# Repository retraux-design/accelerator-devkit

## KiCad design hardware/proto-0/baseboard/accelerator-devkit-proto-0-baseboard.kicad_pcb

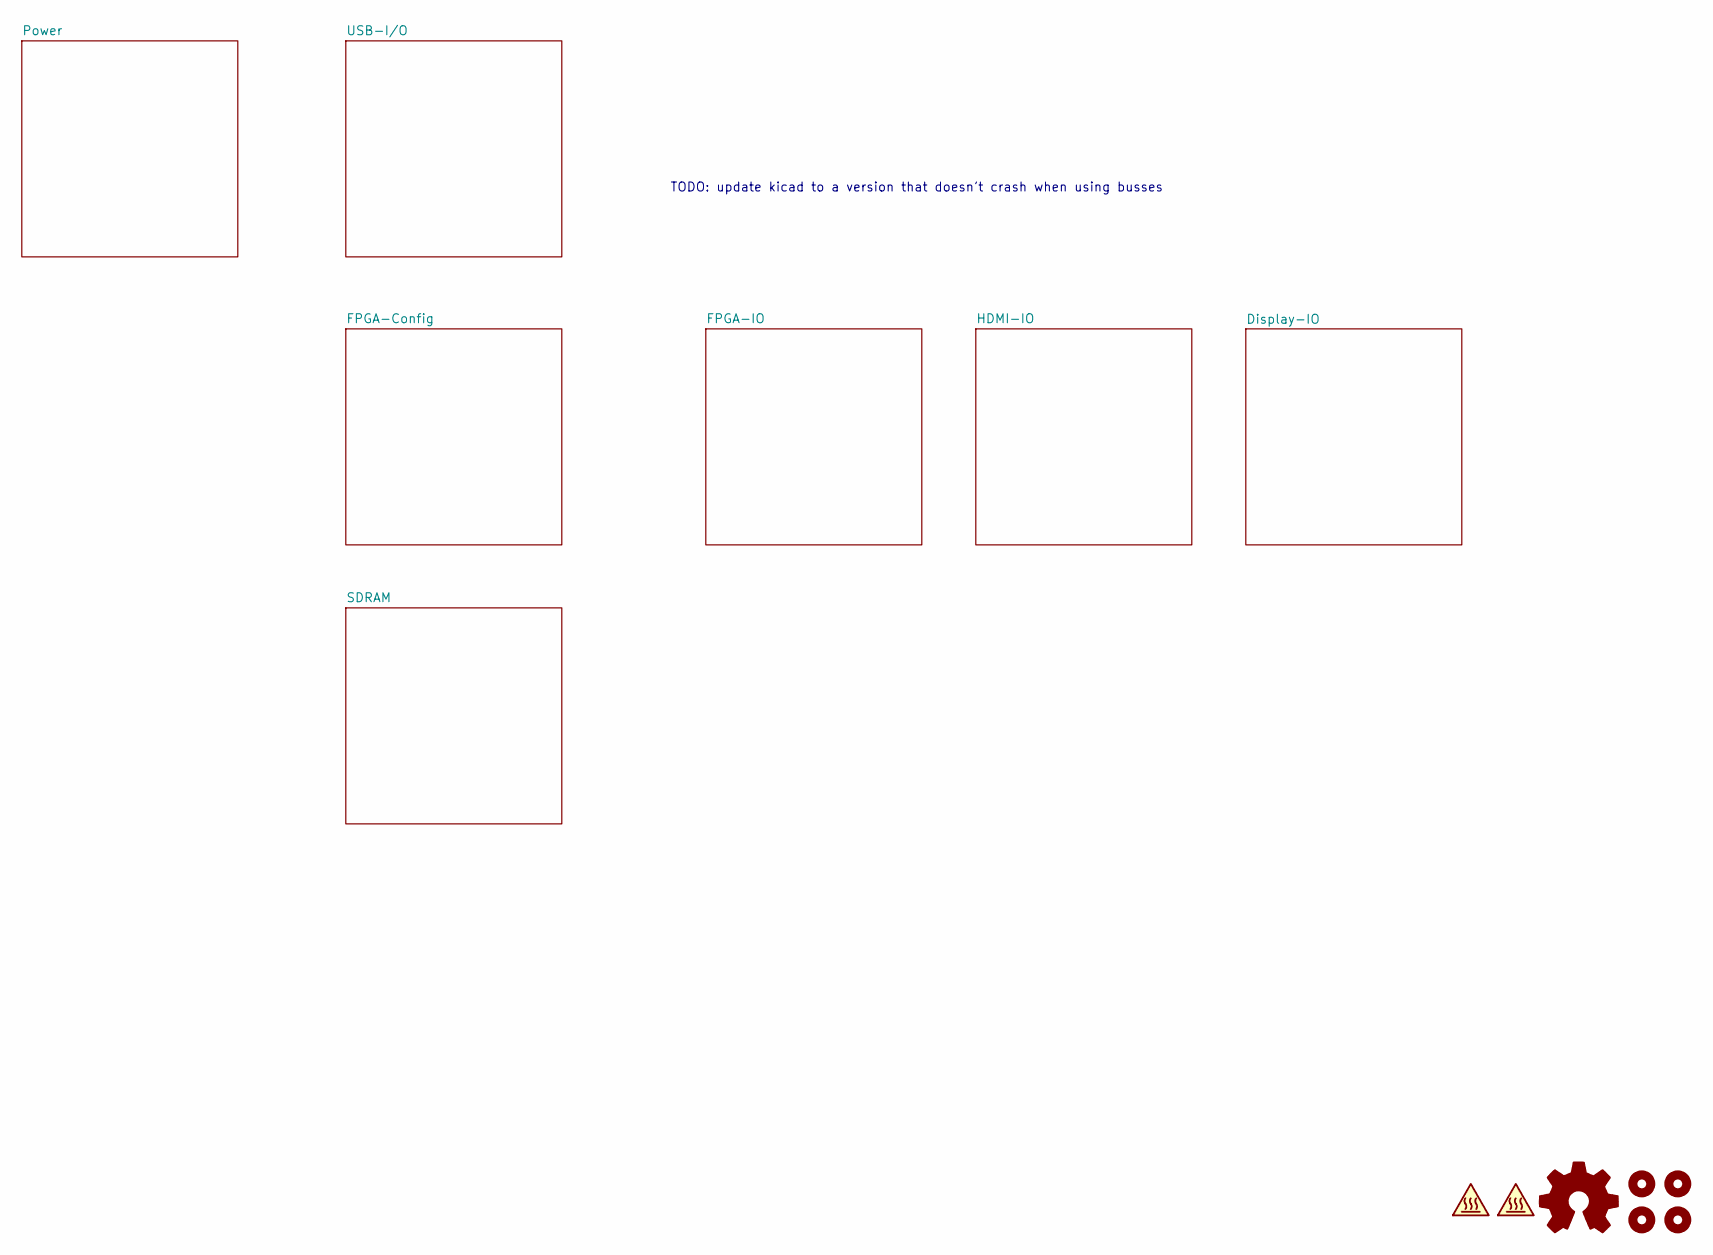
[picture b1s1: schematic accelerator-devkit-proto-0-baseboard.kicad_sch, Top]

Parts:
H1, H2, H3, H4: MountingHole; MountingHole_2.2mm_M2_Pad_Via
LOGO1: Logo_Open_Hardware_Small; OSHW-Symbol_6.7x6mm_Copper
LOGO2, LOGO3: SYM_Hot_Small; OSHW-Logo2_7.3x6mm_Copper

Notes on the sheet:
TODO: update kicad to a version that doesn't crash when using busses

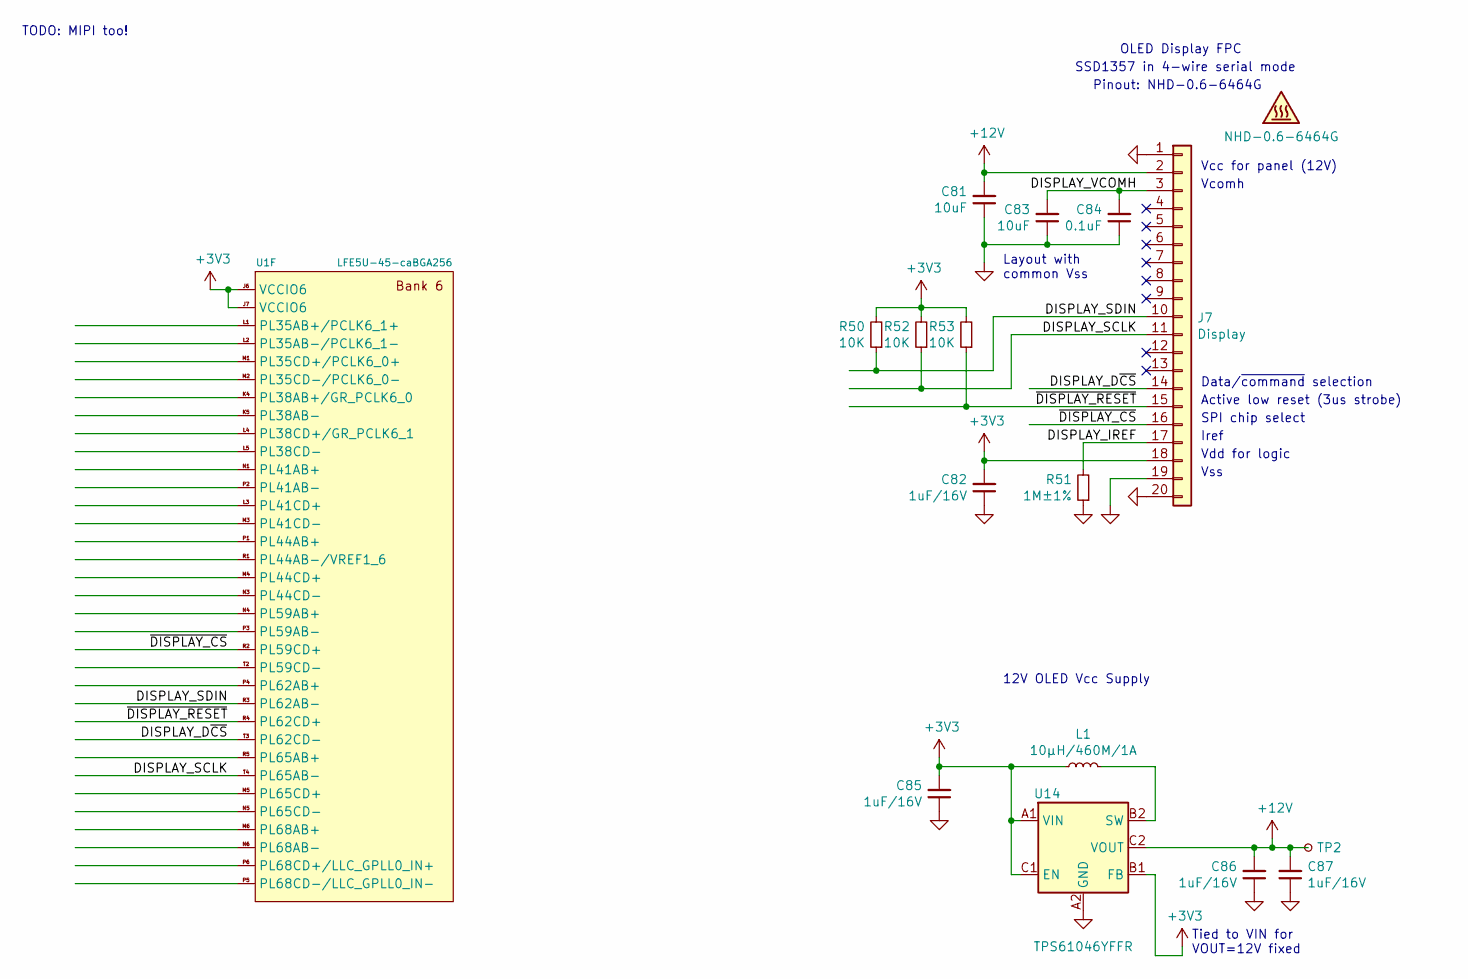
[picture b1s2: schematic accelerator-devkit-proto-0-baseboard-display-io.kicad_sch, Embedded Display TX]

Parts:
C81, C83: 10uF; C_0402_1005Metric
C82, C85, C86, C87: 1uF/16V; C_0402_1005Metric
C84: 0.1uF; C_0402_1005Metric
DISPLAY1: NHD-0.6-6464G
J7: Display; Molex_FFC-FPC_52745-2033_1x20_P0.5mm_TopContact
L1: 10µH/460M/1A; L_1008_2520Metric; Part 1239AS-H-100M=P2
R50, R52, R53: 10K; R_0402_1005Metric
R51: 1M±1%; R_0402_1005Metric
TP2: TestPoint_Small; TestPoint_THTPad_D1.0mm_Drill0.5mm
U1: LFE5U-45-caBGA256; Lattice_caBGA-256_14x14mm_P0.8mm
U14: TPS61046YFFR; Texas_DSBGA-6_0.8x1.2mm_Layout2x3_P0.4mm

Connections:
+3V3: C82.2, C85.2, J7.18, L1.1, R50.2, R52.2, R53.2, U1.J6 (VCCIO6), U1.J7 (VCCIO6), U14.A1 (VIN), U14.B1 (FB), U14.C1 (EN); also elsewhere on the board
+12V: C81.2, C86.2, C87.2, J7.2, TP2.1, U14.C2 (VOUT)
/Display-IO/DISPLAY_D~CS: J7.14, U1.T3 (PL62CD-)
/Display-IO/DISPLAY_IREF: J7.17, R51.2
/Display-IO/DISPLAY_SCLK: J7.11, R52.1, U1.T4 (PL65AB-)
/Display-IO/DISPLAY_SDIN: J7.10, R50.1, U1.R3 (PL62AB-)
/Display-IO/DISPLAY_VCOMH: C83.2, C84.2, J7.3
/Display-IO/~DISPLAY_CS: J7.16, U1.R2 (PL59CD+)
/Display-IO/~DISPLAY_RESET: J7.15, R53.1, U1.R4 (PL62CD+)
GND: C81.1, C82.1, C83.1, C84.1, C85.1, C86.1, C87.1, J7.1, J7.19, J7.20, R51.1, U14.A2 (GND); also elsewhere on the board
unnamed: L1.2, U14.B2 (SW)

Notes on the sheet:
TODO: MIPI too!
Layout with common Vss
12V OLED Vcc Supply
SSD1357 in 4-wire serial mode
Pinout: NHD-0.6-6464G
OLED Display FPC
Tied to VIN for VOUT=12V fixed
Vcc for panel (12V)
Vcomh
Data/~command~ selection
Active low reset (3us strobe)
SPI chip select
Iref
Vdd for logic
Vss

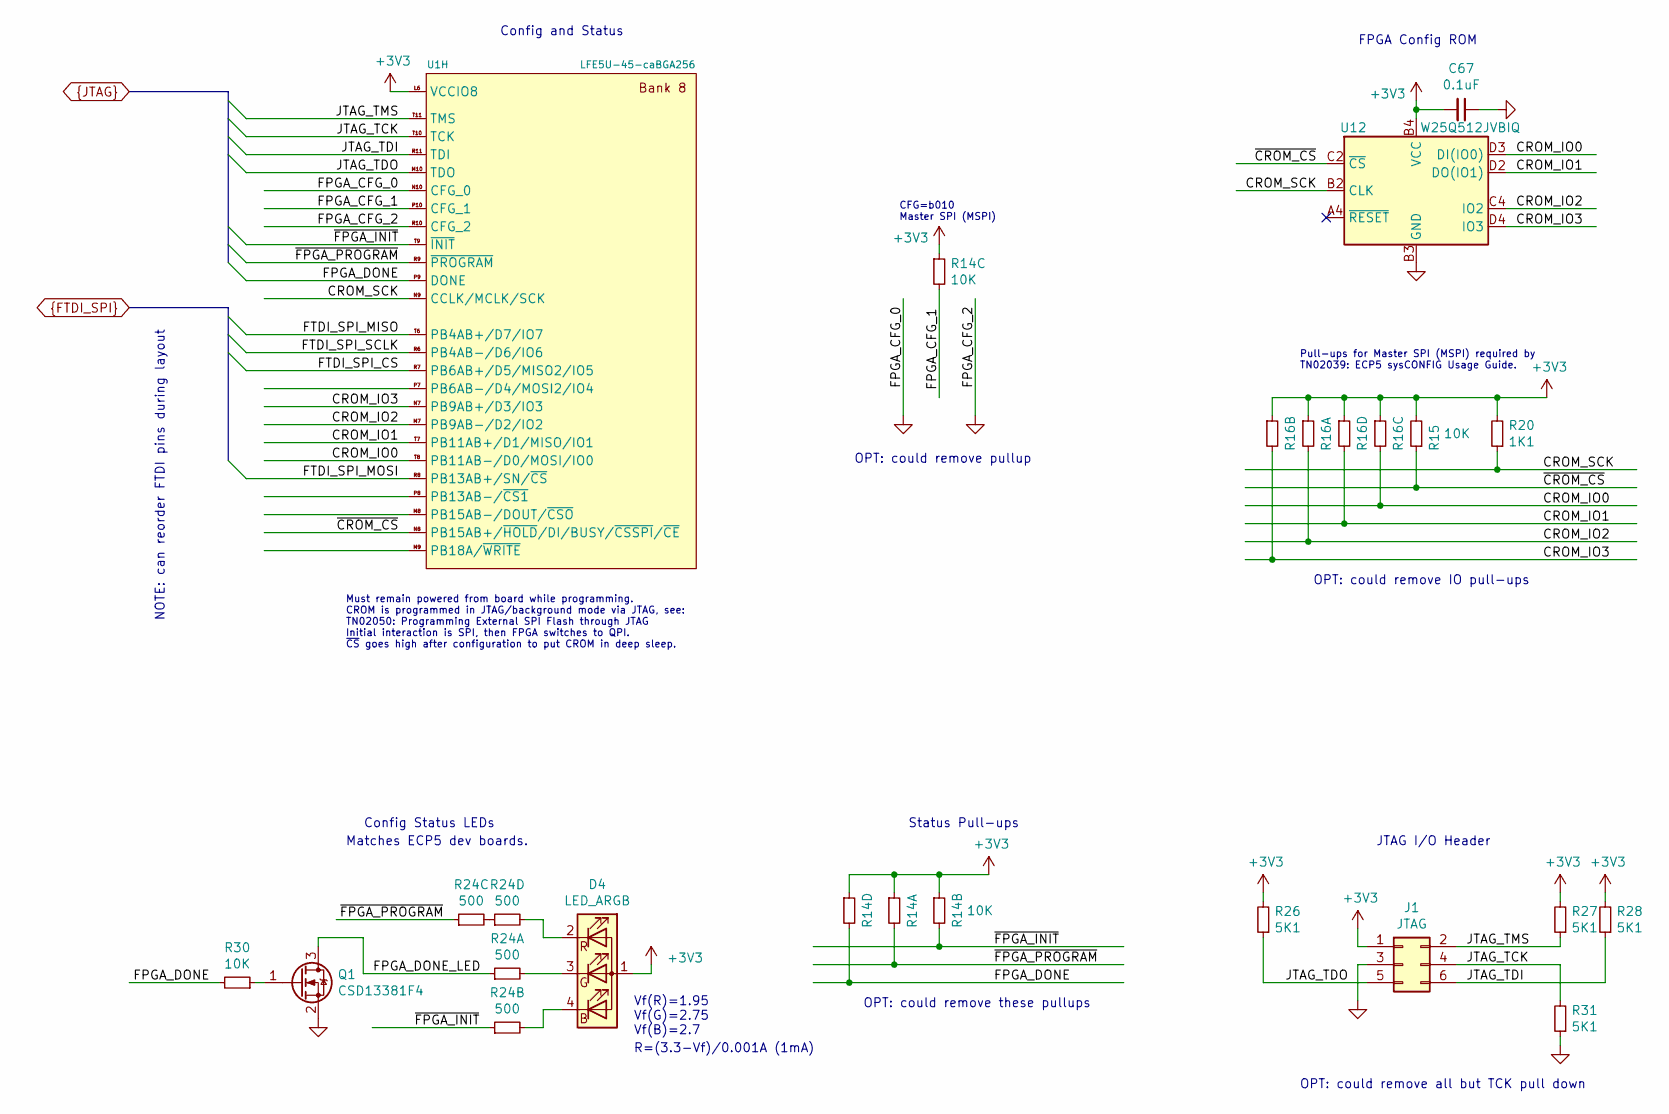
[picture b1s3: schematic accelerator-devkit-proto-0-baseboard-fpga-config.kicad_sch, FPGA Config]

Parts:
C67: 0.1uF; C_0402_1005Metric
D4: LED_ARGB; SML-LX0404SIUPGUSB; Part SML-LX0404SIUPGUSB
J1: JTAG; Tag-Connect_TC2030-IDC-NL_2x03_P1.27mm_Vertical_Outlined
Q1: CSD13381F4; Texas_DFN100X60X35-3N
R14, R16: 10K; R_Array_Concave_4x0402
R15, R30: 10K; R_0402_1005Metric
R20: 1K1; R_0402_1005Metric
R24: 500; R_Array_Concave_4x0402
R26, R27, R28, R31: 5K1; R_0402_1005Metric
U1: LFE5U-45-caBGA256; Lattice_caBGA-256_14x14mm_P0.8mm
U12: W25Q512JVBIQ; Winbond_TFBGA-24-5x5mm_P1.0mm

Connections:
+3V3: C67.2, D4.1 (A), J1.1, R14.1, R14.2, R14.3, R14.4, R15.2, R16.1, R16.2, R16.3, R16.4, R20.2, R26.2, R27.2, R28.2, U1.L6 (VCCIO8), U12.B4 (VCC); also elsewhere on the board
/FPGA-Config/CROM_IO0: R16.6, U1.T8 (PB11AB-/D0/MOSI/IO0), U12.D3 (DI(IO0))
/FPGA-Config/CROM_IO1: R16.5, U1.T7 (PB11AB+/D1/MISO/IO1), U12.D2 (DO(IO1))
/FPGA-Config/CROM_IO2: R16.8, U1.M7 (PB9AB-/D2/IO2), U12.C4 (IO2)
/FPGA-Config/CROM_IO3: R16.7, U1.N7 (PB9AB+/D3/IO3), U12.D4 (IO3)
/FPGA-Config/CROM_SCK: R20.1, U1.N9 (CCLK/MCLK/SCK), U12.B2 (CLK)
/FPGA-Config/FPGA_CFG_1: R14.6, U1.P10 (CFG_1)
/FPGA-Config/FPGA_DONE_LED: Q1.3 (D), R24.1
/FPGA-Config/~CROM_CS: R15.1, U1.N8 (PB15AB+/~HOLD~/DI/BUSY/~CSSPI~/~CE~), U12.C2 (~CS)
FPGA_DONE: R14.5, R30.2, U1.P9 (DONE); also elsewhere on the board
FTDI_SPI_CS: U1.R7 (PB6AB+/D5/MISO2/IO5); also elsewhere on the board
FTDI_SPI_MISO: U1.T6 (PB4AB+/D7/IO7); also elsewhere on the board
FTDI_SPI_MOSI: U1.R8 (PB13AB+/SN/~CS); also elsewhere on the board
FTDI_SPI_SCLK: U1.R6 (PB4AB-/D6/IO6); also elsewhere on the board
GND: C67.1, J1.3, Q1.2 (S), R31.1, U1.N10 (CFG_0), U1.R10 (CFG_2), U12.B3 (GND); also elsewhere on the board
JTAG_TCK: J1.4, R31.2, U1.T10 (TCK); also elsewhere on the board
JTAG_TDI: J1.6, R28.1, U1.R11 (TDI); also elsewhere on the board
JTAG_TDO: J1.5, R26.1, U1.M10 (TDO); also elsewhere on the board
JTAG_TMS: J1.2, R27.1, U1.T11 (TMS); also elsewhere on the board
unnamed: D4.2 (RK), R24.5
unnamed: D4.3 (GK), R24.8
unnamed: D4.4 (BK), R24.7
unnamed: Q1.1 (G), R30.1
unnamed: R24.4, R24.6
~FPGA_INIT: R14.7, R24.2, U1.T9 (~INIT); also elsewhere on the board
~FPGA_PROGRAM: R14.8, R24.3, U1.R9 (~PROGRAM); also elsewhere on the board

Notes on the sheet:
NOTE: can reorder FTDI pins during layout
Must remain powered from board while programming. CROM is programmed in JTAG/background mode via JTAG, see: TN02050: Programming External SPI Flash through JTAG Initial interaction is SPI, then FPGA switches to QPI. ~CS~ goes high after configuration to put CROM in deep sleep.
Matches ECP5 dev boards.
Config Status LEDs
Config and Status
Vf(R)=1.95 Vf(G)=2.75 Vf(B)=2.7
R=(3.3-Vf)/0.001A (1mA)
OPT: could remove pullup
OPT: could remove these pullups
CFG=b010 Master SPI (MSPI)
Status Pull-ups
Pull-ups for Master SPI (MSPI) required by TN02039: ECP5 sysCONFIG Usage Guide.
OPT: could remove all but TCK pull down
OPT: could remove IO pull-ups
FPGA Config ROM
JTAG I/O Header

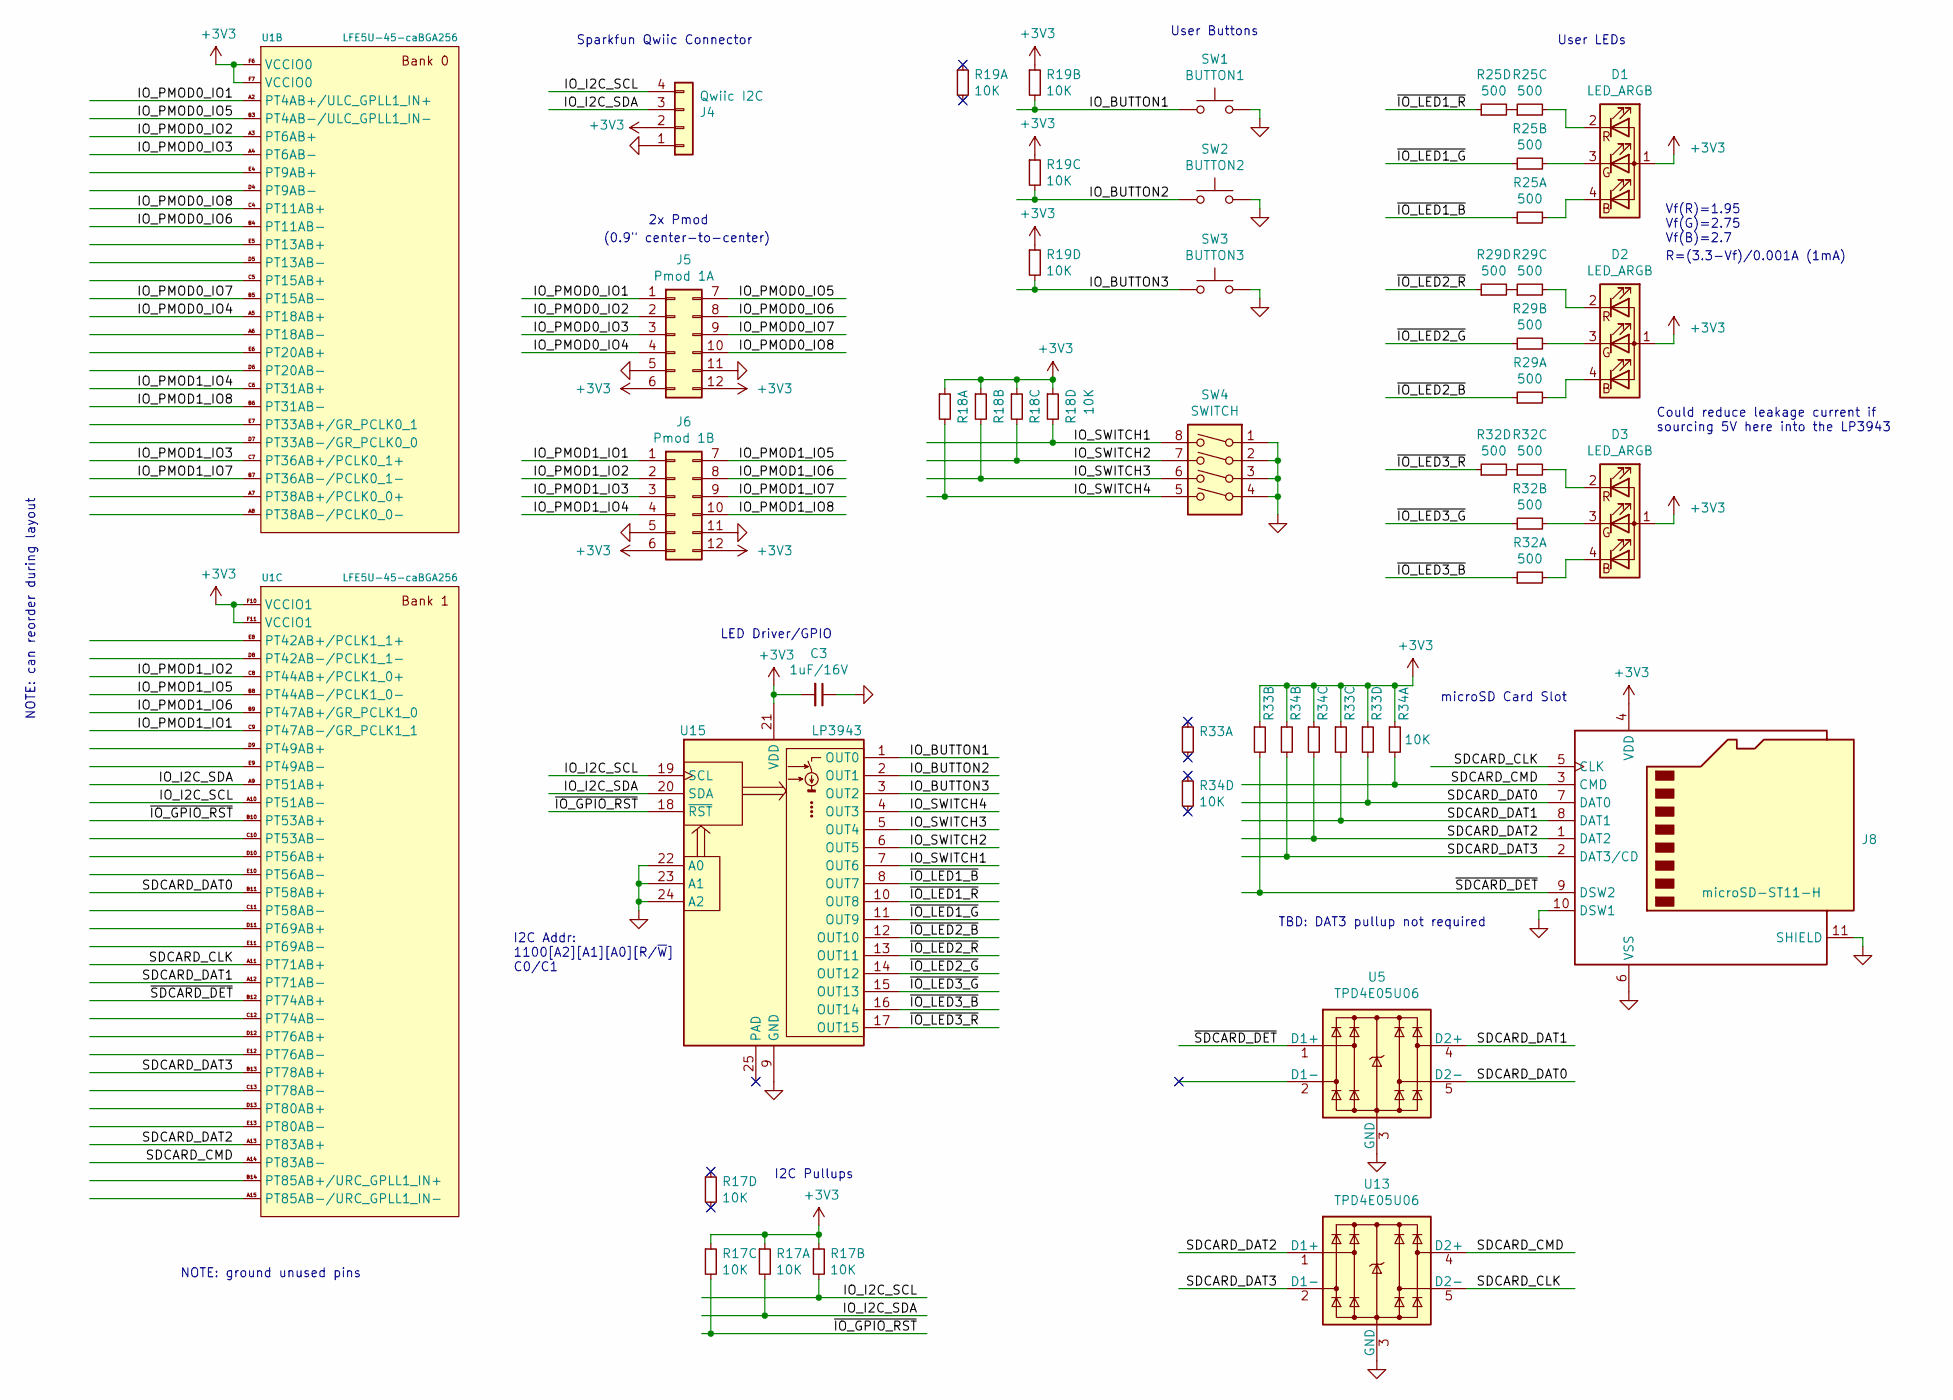
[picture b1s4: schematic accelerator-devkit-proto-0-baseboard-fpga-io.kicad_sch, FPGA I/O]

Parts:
C3: 1uF/16V; C_0402_1005Metric
D1, D2, D3: LED_ARGB; SML-LX0404SIUPGUSB; Part SML-LX0404SIUPGUSB
J4: Qwiic I2C; Qwiic_JST_SH_BM04B-SRSS-TB_1x04-1MP_P1.00mm_Vertical
J5: Pmod 1A; Pmod_2Stacked_PinSocket_2x06_P2.54mm_Horizontal
J6: Pmod 1B; Pmod_2Stacked_PinSocket_2x06_P2.54mm_Horizontal
J8: microSD-ST11-H; microSD_HC_JAE_ST11-H_ST11S008V4HR2000
R17, R18, R19, R33, R34: 10K; R_Array_Concave_4x0402
R25, R29, R32: 500; R_Array_Concave_4x0402
SW1: BUTTON1; PTS830GG140SMTRLFS; Part PTS830GM140
SW2: BUTTON2; PTS830GG140SMTRLFS; Part PTS830GM140
SW3: BUTTON3; PTS830GG140SMTRLFS; Part PTS830GM140
SW4: SWITCH; CVS-04TB; Part CVS-04TB
U1: LFE5U-45-caBGA256; Lattice_caBGA-256_14x14mm_P0.8mm
U5, U13: TPD4E05U06; USON-10_2.5x1.0mm_P0.5mm
U15: LP3943; Texas_S-PVQFN-N24_EP2.1x2.1mm

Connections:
+3V3: C3.2, D1.1 (A), D2.1 (A), D3.1 (A), J4.2, J5.6, J5.12, J6.6, J6.12, J8.4 (VDD), R17.1, R17.2, R17.3, R18.1, R18.2, R18.3, R18.4, R19.2, R19.3, R19.4, R33.2, R33.3, R33.4, R34.1, R34.2, R34.3, U1.F6 (VCCIO0), U1.F7 (VCCIO0), U1.F10 (VCCIO1), U1.F11 (VCCIO1), U15.21 (VDD); also elsewhere on the board
/FPGA-IO/IO_BUTTON1: R19.7, SW1.1, SW1.3, U15.1 (OUT0)
/FPGA-IO/IO_BUTTON2: R19.6, SW2.1, SW2.3, U15.2 (OUT1)
/FPGA-IO/IO_BUTTON3: R19.5, SW3.1, SW3.3, U15.3 (OUT2)
/FPGA-IO/IO_I2C_SCL: J4.4, R17.7, U1.A10 (PT51AB-), U15.19 (SCL)
/FPGA-IO/IO_I2C_SDA: J4.3, R17.8, U1.A9 (PT51AB+), U15.20 (SDA)
/FPGA-IO/IO_PMOD0_IO1: J5.1, U1.A2 (PT4AB+/ULC_GPLL1_IN+)
/FPGA-IO/IO_PMOD0_IO2: J5.2, U1.A3 (PT6AB+)
/FPGA-IO/IO_PMOD0_IO3: J5.3, U1.A4 (PT6AB-)
/FPGA-IO/IO_PMOD0_IO4: J5.4, U1.A5 (PT18AB+)
/FPGA-IO/IO_PMOD0_IO5: J5.7, U1.B3 (PT4AB-/ULC_GPLL1_IN-)
/FPGA-IO/IO_PMOD0_IO6: J5.8, U1.B4 (PT11AB-)
/FPGA-IO/IO_PMOD0_IO7: J5.9, U1.B5 (PT15AB-)
/FPGA-IO/IO_PMOD0_IO8: J5.10, U1.C4 (PT11AB+)
/FPGA-IO/IO_PMOD1_IO1: J6.1, U1.C9 (PT47AB-/GR_PCLK1_1)
/FPGA-IO/IO_PMOD1_IO2: J6.2, U1.C8 (PT44AB+/PCLK1_0+)
/FPGA-IO/IO_PMOD1_IO3: J6.3, U1.C7 (PT36AB+/PCLK0_1+)
/FPGA-IO/IO_PMOD1_IO4: J6.4, U1.C6 (PT31AB+)
/FPGA-IO/IO_PMOD1_IO5: J6.7, U1.B8 (PT44AB-/PCLK1_0-)
/FPGA-IO/IO_PMOD1_IO6: J6.8, U1.B9 (PT47AB+/GR_PCLK1_0)
/FPGA-IO/IO_PMOD1_IO7: J6.9, U1.B7 (PT36AB-/PCLK0_1-)
/FPGA-IO/IO_PMOD1_IO8: J6.10, U1.B6 (PT31AB-)
/FPGA-IO/IO_SWITCH1: R18.5, SW4.8, U15.7 (OUT6)
/FPGA-IO/IO_SWITCH2: R18.6, SW4.7, U15.6 (OUT5)
/FPGA-IO/IO_SWITCH3: R18.7, SW4.6, U15.5 (OUT4)
/FPGA-IO/IO_SWITCH4: R18.8, SW4.5, U15.4 (OUT3)
/FPGA-IO/SDCARD_CLK: J8.5 (CLK), U1.A11 (PT71AB+), U13.5 (D2-), U13.6 (D2-)
/FPGA-IO/SDCARD_CMD: J8.3 (CMD), R34.8, U1.A14 (PT83AB-), U13.4 (D2+), U13.7 (D2+)
/FPGA-IO/SDCARD_DAT0: J8.7 (DAT0), R33.5, U1.B11 (PT58AB+), U5.5 (D2-), U5.6 (D2-)
/FPGA-IO/SDCARD_DAT1: J8.8 (DAT1), R33.6, U1.A12 (PT71AB-), U5.4 (D2+), U5.7 (D2+)
/FPGA-IO/SDCARD_DAT2: J8.1 (DAT2), R34.6, U1.A13 (PT83AB+), U13.1 (D1+), U13.10 (D1+)
/FPGA-IO/SDCARD_DAT3: J8.2 (DAT3/CD), R34.7, U1.B13 (PT78AB+), U13.2 (D1-), U13.9 (D1-)
/FPGA-IO/~IO_GPIO_RST: R17.6, U1.B10 (PT53AB+), U15.18 (~RST)
/FPGA-IO/~IO_LED1_B: R25.1, U15.8 (OUT7)
/FPGA-IO/~IO_LED1_G: R25.2, U15.11 (OUT9)
/FPGA-IO/~IO_LED1_R: R25.4, U15.10 (OUT8)
/FPGA-IO/~IO_LED2_B: R29.1, U15.12 (OUT10)
/FPGA-IO/~IO_LED2_G: R29.2, U15.14 (OUT12)
/FPGA-IO/~IO_LED2_R: R29.4, U15.13 (OUT11)
/FPGA-IO/~IO_LED3_B: R32.1, U15.16 (OUT14)
/FPGA-IO/~IO_LED3_G: R32.2, U15.15 (OUT13)
/FPGA-IO/~IO_LED3_R: R32.4, U15.17 (OUT15)
/FPGA-IO/~SDCARD_DET: J8.9 (DSW2), R33.7, U1.B12 (PT74AB+), U5.1 (D1+), U5.10 (D1+)
GND: C3.1, J4.1, J5.5, J5.11, J6.5, J6.11, J8.6 (VSS), J8.10 (DSW1), J8.11 (SHIELD), SW1.2, SW1.4, SW2.2, SW2.4, SW3.2, SW3.4, SW4.1, SW4.2, SW4.3, SW4.4, U5.3 (GND), U5.8 (GND), U13.3 (GND), U13.8 (GND), U15.9 (GND), U15.22 (A0), U15.23 (A1), U15.24 (A2); also elsewhere on the board
unnamed: D1.2 (RK), R25.6
unnamed: D1.3 (GK), R25.7
unnamed: D1.4 (BK), R25.8
unnamed: D2.2 (RK), R29.6
unnamed: D2.3 (GK), R29.7
unnamed: D2.4 (BK), R29.8
unnamed: D3.2 (RK), R32.6
unnamed: D3.3 (GK), R32.7
unnamed: D3.4 (BK), R32.8
unnamed: R25.3, R25.5
unnamed: R29.3, R29.5
unnamed: R32.3, R32.5
unnamed: U5.2 (D1-), U5.9 (D1-)

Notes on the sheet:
NOTE: can reorder during layout
NOTE: ground unused pins
I2C Addr: 1100[A2][A1][A0][R/~W~] C0/C1
Sparkfun Qwiic Connector
(0.9" center-to-center)
2x Pmod
LED Driver/GPIO
I2C Pullups
User Buttons
TBD: DAT3 pullup not required
microSD Card Slot
User LEDs
Could reduce leakage current if sourcing 5V here into the LP3943
Vf(R)=1.95 Vf(G)=2.75 Vf(B)=2.7
R=(3.3-Vf)/0.001A (1mA)

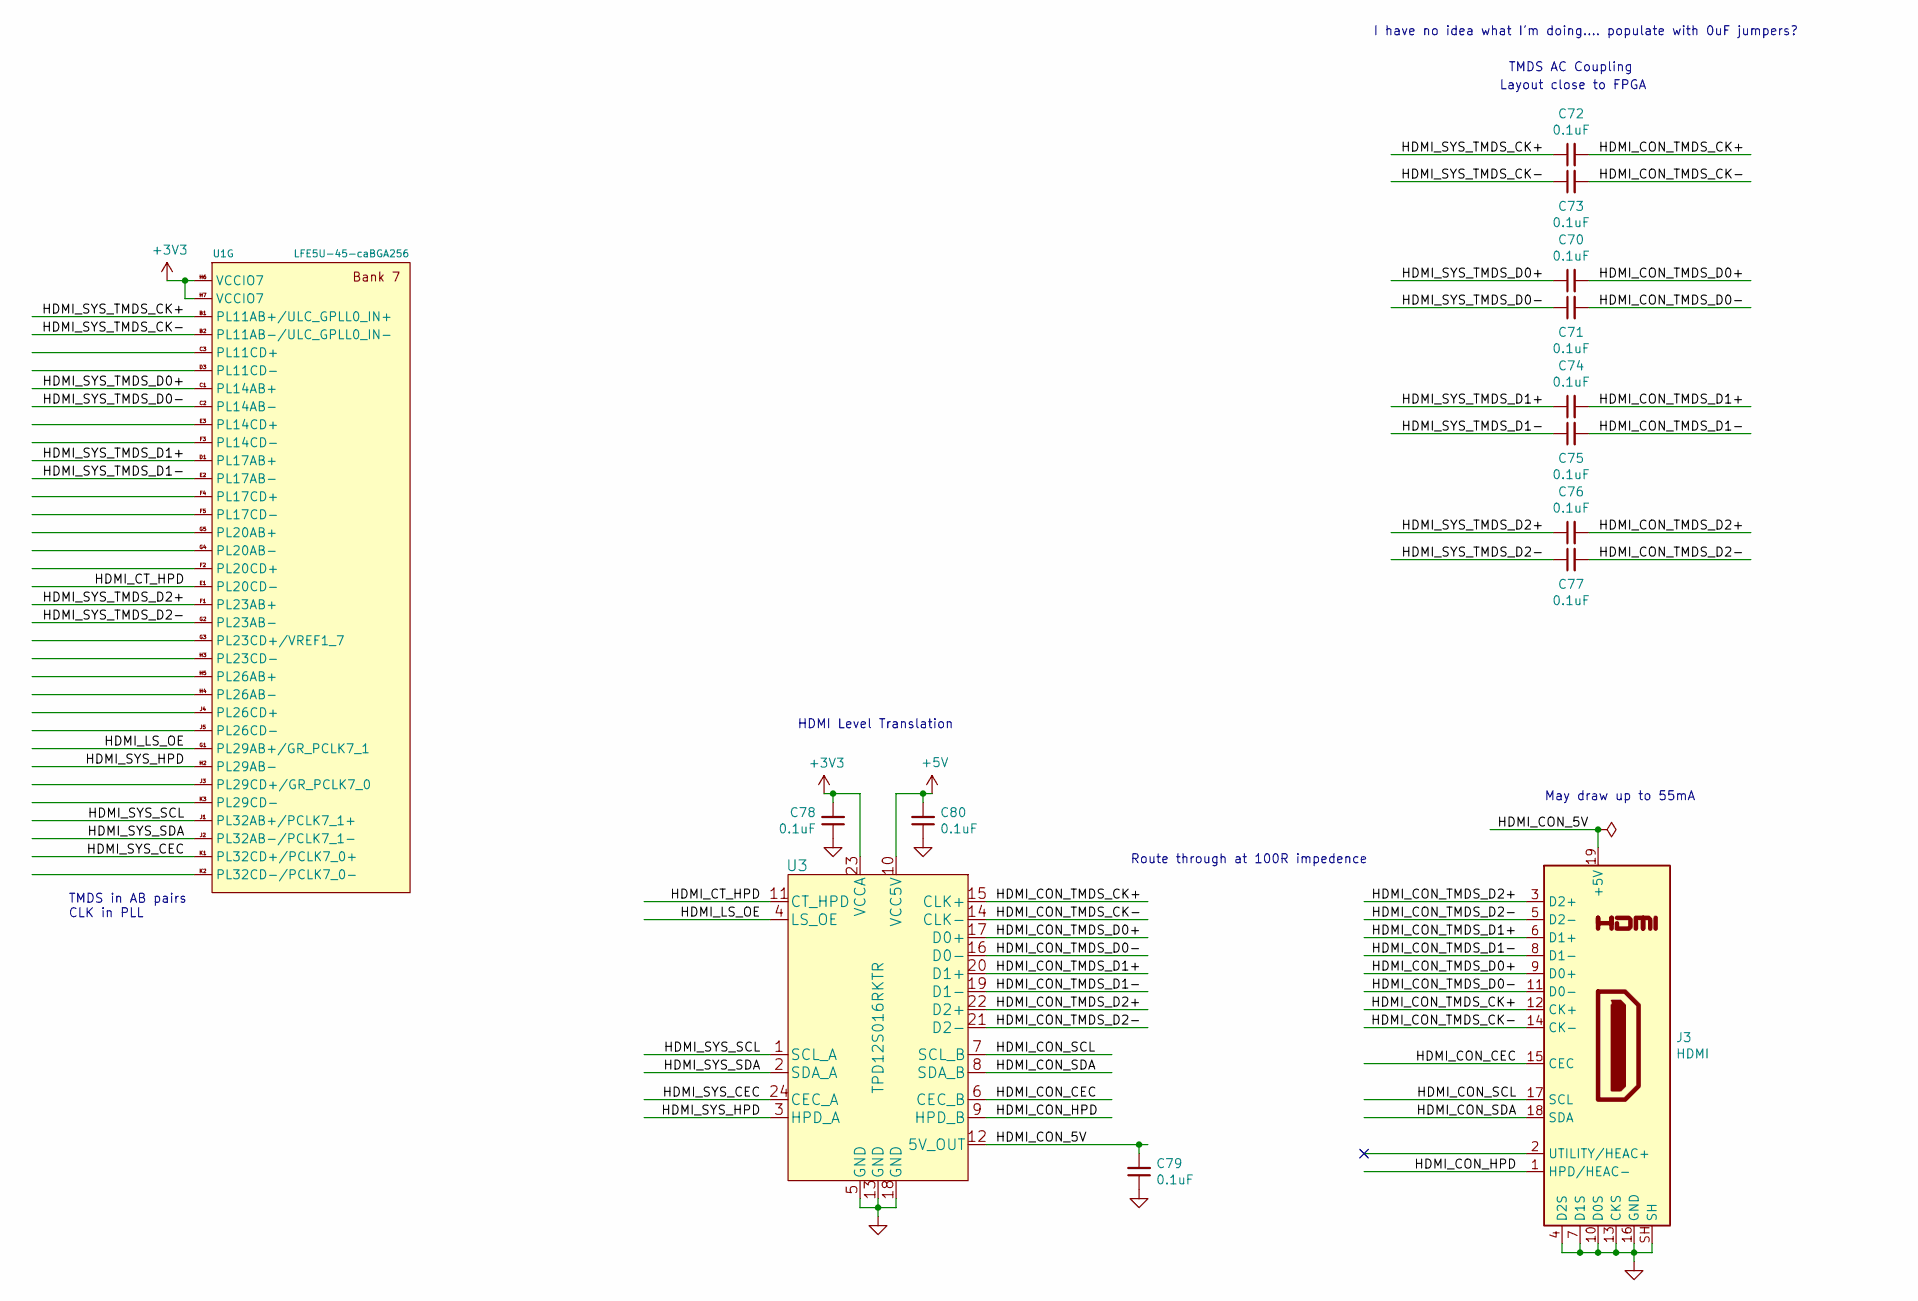
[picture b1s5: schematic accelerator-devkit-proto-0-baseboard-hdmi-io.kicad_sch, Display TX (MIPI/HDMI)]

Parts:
C70, C71, C72, C73, C74, C75, C76, C77: 0.1uF; C_0201_0603Metric
C78, C79, C80: 0.1uF; C_0402_1005Metric
J3: HDMI; HDMI_Micro-D_Molex_46765-0x01
U1: LFE5U-45-caBGA256; Lattice_caBGA-256_14x14mm_P0.8mm
U3: TPD12S016RKTR; Texas_UQFN-24_4x2mm_P0.4mm_RKTR

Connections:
+3V3: C78.2, U1.H6 (VCCIO7), U1.H7 (VCCIO7), U3.23 (VCCA); also elsewhere on the board
+5V: C80.2, U3.10 (VCC5V); also elsewhere on the board
/HDMI-IO/HDMI_CON_5V: C79.2, J3.19 (+5V), U3.12 (5V_OUT)
/HDMI-IO/HDMI_CON_CEC: J3.15 (CEC), U3.6 (CEC_B)
/HDMI-IO/HDMI_CON_HPD: J3.1 (HPD/HEAC-), U3.9 (HPD_B)
/HDMI-IO/HDMI_CON_SCL: J3.17 (SCL), U3.7 (SCL_B)
/HDMI-IO/HDMI_CON_SDA: J3.18 (SDA), U3.8 (SDA_B)
/HDMI-IO/HDMI_CON_TMDS_CK+: C72.2, J3.12 (CK+), U3.15 (CLK+)
/HDMI-IO/HDMI_CON_TMDS_CK-: C73.2, J3.14 (CK-), U3.14 (CLK-)
/HDMI-IO/HDMI_CON_TMDS_D0+: C70.2, J3.9 (D0+), U3.17 (D0+)
/HDMI-IO/HDMI_CON_TMDS_D0-: C71.2, J3.11 (D0-), U3.16 (D0-)
/HDMI-IO/HDMI_CON_TMDS_D1+: C74.2, J3.6 (D1+), U3.20 (D1+)
/HDMI-IO/HDMI_CON_TMDS_D1-: C75.2, J3.8 (D1-), U3.19 (D1-)
/HDMI-IO/HDMI_CON_TMDS_D2+: C76.2, J3.3 (D2+), U3.22 (D2+)
/HDMI-IO/HDMI_CON_TMDS_D2-: C77.2, J3.5 (D2-), U3.21 (D2-)
/HDMI-IO/HDMI_CT_HPD: U1.E1 (PL20CD-), U3.11 (CT_HPD)
/HDMI-IO/HDMI_LS_OE: U1.G1 (PL29AB+/GR_PCLK7_1), U3.4 (LS_OE)
/HDMI-IO/HDMI_SYS_CEC: U1.K1 (PL32CD+/PCLK7_0+), U3.24 (CEC_A)
/HDMI-IO/HDMI_SYS_HPD: U1.H2 (PL29AB-), U3.3 (HPD_A)
/HDMI-IO/HDMI_SYS_SCL: U1.J1 (PL32AB+/PCLK7_1+), U3.1 (SCL_A)
/HDMI-IO/HDMI_SYS_SDA: U1.J2 (PL32AB-/PCLK7_1-), U3.2 (SDA_A)
/HDMI-IO/HDMI_SYS_TMDS_CK+: C72.1, U1.B1 (PL11AB+/ULC_GPLL0_IN+)
/HDMI-IO/HDMI_SYS_TMDS_CK-: C73.1, U1.B2 (PL11AB-/ULC_GPLL0_IN-)
/HDMI-IO/HDMI_SYS_TMDS_D0+: C70.1, U1.C1 (PL14AB+)
/HDMI-IO/HDMI_SYS_TMDS_D0-: C71.1, U1.C2 (PL14AB-)
/HDMI-IO/HDMI_SYS_TMDS_D1+: C74.1, U1.D1 (PL17AB+)
/HDMI-IO/HDMI_SYS_TMDS_D1-: C75.1, U1.E2 (PL17AB-)
/HDMI-IO/HDMI_SYS_TMDS_D2+: C76.1, U1.F1 (PL23AB+)
/HDMI-IO/HDMI_SYS_TMDS_D2-: C77.1, U1.G2 (PL23AB-)
GND: C78.1, C79.1, C80.1, J3.4 (D2S), J3.7 (D1S), J3.10 (D0S), J3.13 (CKS), J3.16 (GND), J3.SH, U3.5 (GND), U3.13 (GND), U3.18 (GND); also elsewhere on the board

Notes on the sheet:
TMDS in AB pairs CLK in PLL
HDMI Level Translation
Route through at 100R impedence
I have no idea what I'm doing.... populate with 0uF jumpers?
Layout close to FPGA
TMDS AC Coupling
May draw up to 55mA

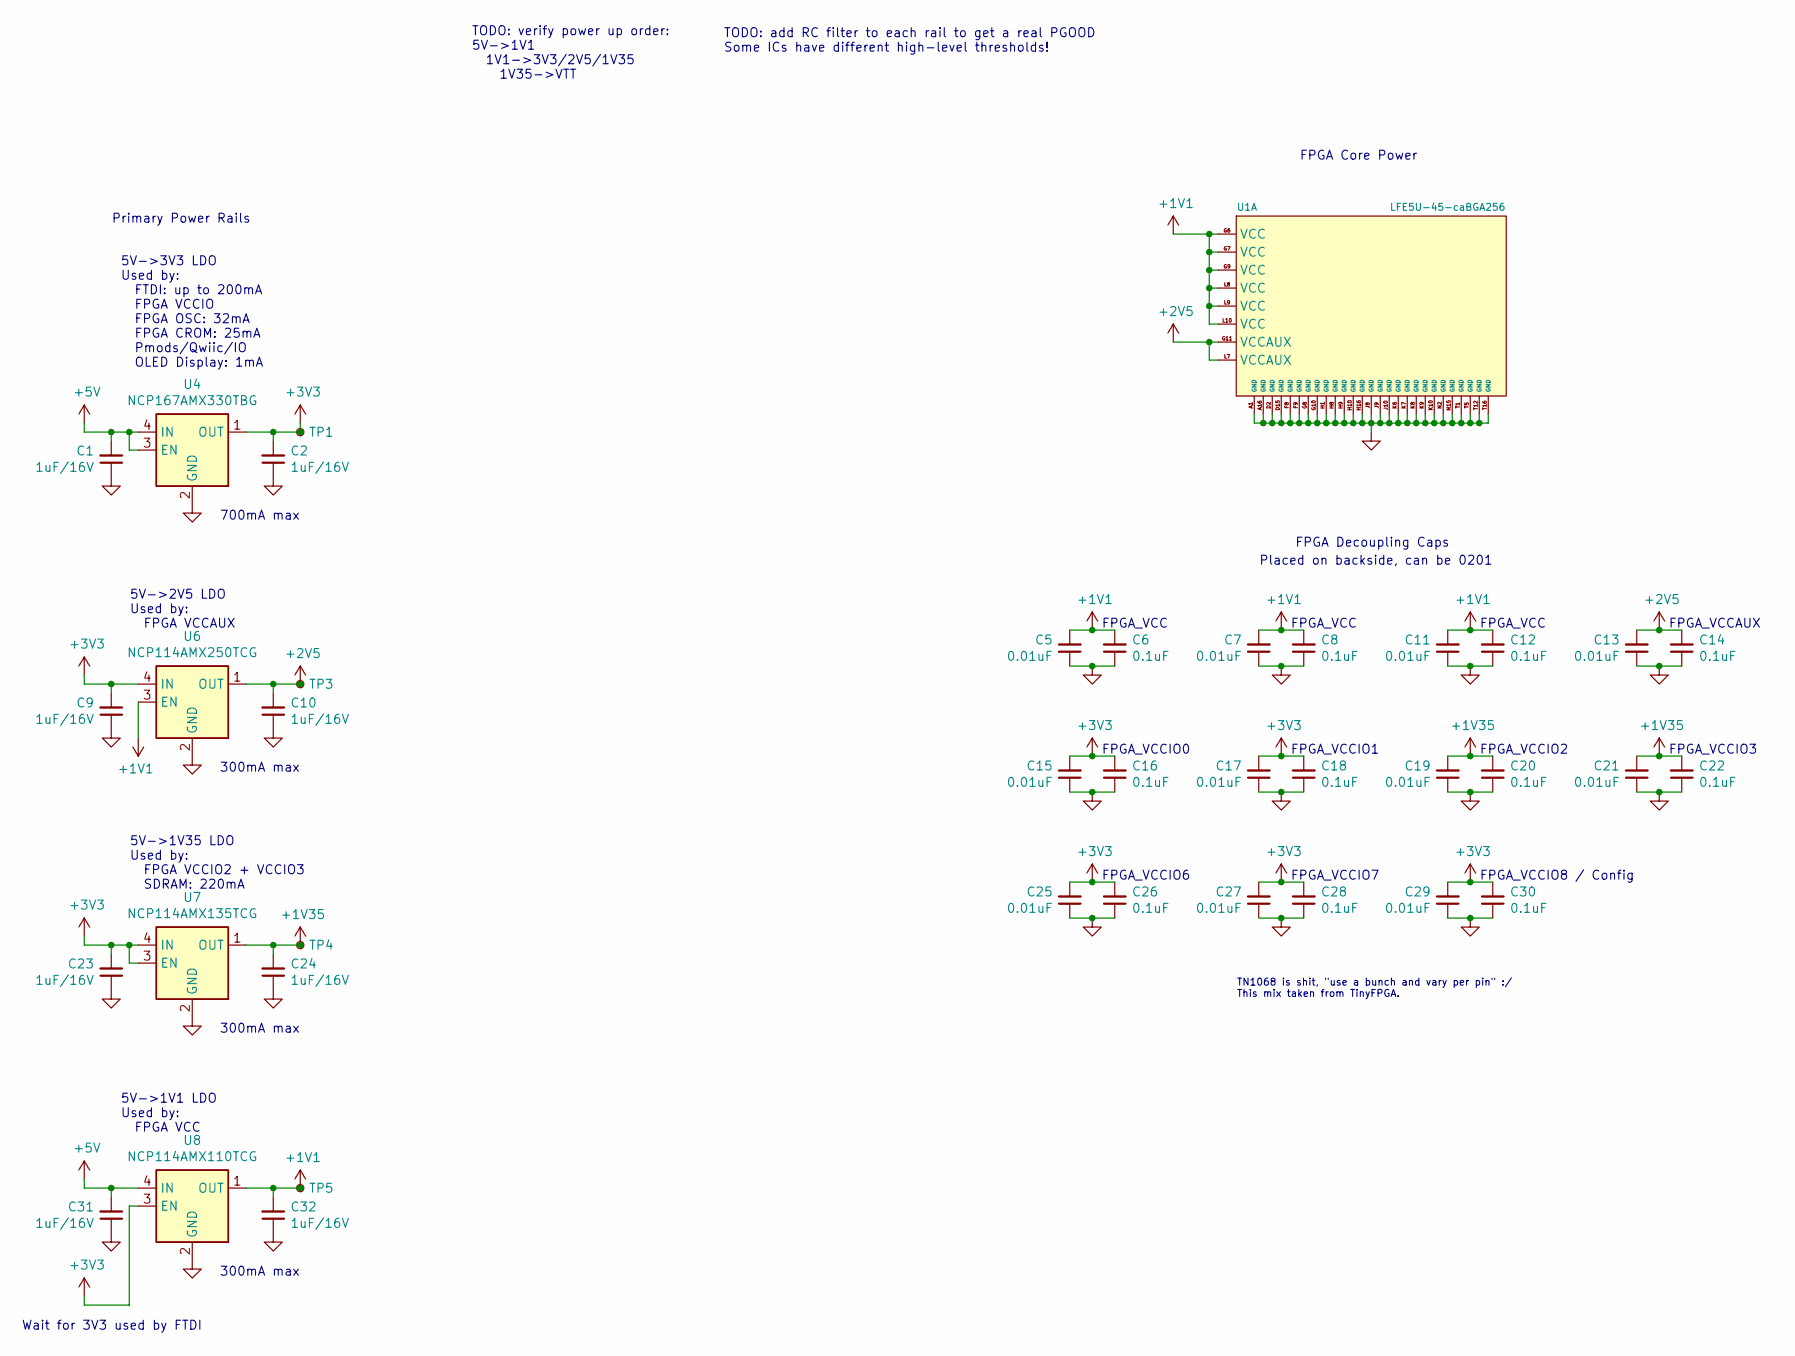
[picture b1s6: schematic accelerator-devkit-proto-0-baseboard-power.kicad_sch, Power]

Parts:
C1, C2, C9, C10, C23, C24, C31, C32: 1uF/16V; C_0402_1005Metric
C5, C7, C11, C13, C15, C17, C19, C21, C25, C27, C29: 0.01uF; C_0201_0603Metric
C6, C8, C12, C14, C16, C18, C20, C22, C26, C28, C30: 0.1uF; C_0201_0603Metric
TP1, TP3, TP4, TP5: TestPoint_Small; TestPoint_THTPad_D1.0mm_Drill0.5mm
U1: LFE5U-45-caBGA256; Lattice_caBGA-256_14x14mm_P0.8mm
U4: NCP167AMX330TBG; XDFN-4-1EP_1x1mm_P0.65mm_EP0.48x0.48mm
U6: NCP114AMX250TCG; UDFN-4-1EP_1x1mm_P0.65mm_EP0.48x0.48mm
U7: NCP114AMX135TCG; UDFN-4-1EP_1x1mm_P0.65mm_EP0.48x0.48mm
U8: NCP114AMX110TCG; UDFN-4-1EP_1x1mm_P0.65mm_EP0.48x0.48mm

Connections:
+1V1: C5.2, C6.2, C7.2, C8.2, C11.2, C12.2, C32.2, TP5.1, U1.G6 (VCC), U1.G7 (VCC), U1.G9 (VCC), U1.L8 (VCC), U1.L9 (VCC), U1.L10 (VCC), U6.3 (EN), U8.1 (OUT)
+1V35: C19.2, C20.2, C21.2, C22.2, C24.2, TP4.1, U7.1 (OUT); also elsewhere on the board
+2V5: C10.2, C13.2, C14.2, TP3.1, U1.G11 (VCCAUX), U1.L7 (VCCAUX), U6.1 (OUT)
+3V3: C2.2, C9.2, C15.2, C16.2, C17.2, C18.2, C23.2, C25.2, C26.2, C27.2, C28.2, C29.2, C30.2, TP1.1, U4.1 (OUT), U6.4 (IN), U7.3 (EN), U7.4 (IN), U8.3 (EN); also elsewhere on the board
+5V: C1.2, C31.2, U4.3 (EN), U4.4 (IN), U8.4 (IN); also elsewhere on the board
GND: C1.1, C2.1, C5.1, C6.1, C7.1, C8.1, C9.1, C10.1, C11.1, C12.1, C13.1, C14.1, C15.1, C16.1, C17.1, C18.1, C19.1, C20.1, C21.1, C22.1, C23.1, C24.1, C25.1, C26.1, C27.1, C28.1, C29.1, C30.1, C31.1, C32.1, U1.A1 (GND), U1.A16 (GND), U1.D2 (GND), U1.D15 (GND), U1.F8 (GND), U1.F9 (GND), U1.G8 (GND), U1.G10 (GND), U1.H1 (GND), U1.H8 (GND), U1.H9 (GND), U1.H10 (GND), U1.H16 (GND), U1.J8 (GND), U1.J9 (GND), U1.J10 (GND), U1.K6 (GND), U1.K7 (GND), U1.K8 (GND), U1.K9 (GND), U1.K10 (GND), U1.N2 (GND), U1.N15 (GND), U1.T1 (GND), U1.T5 (GND), U1.T12 (GND), U1.T16 (GND), U4.2 (GND), U4.5 (EPAD), U6.2 (GND), U6.5 (EPAD), U7.2 (GND), U7.5 (EPAD), U8.2 (GND), U8.5 (EPAD); also elsewhere on the board

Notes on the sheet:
Wait for 3V3 used by FTDI
Primary Power Rails
5V->3V3 LDO Used by: FTDI: up to 200mA FPGA VCCIO FPGA OSC: 32mA FPGA CROM: 25mA Pmods/Qwiic/IO OLED Display: 1mA
5V->1V1 LDO Used by: FPGA VCC
5V->2V5 LDO Used by: FPGA VCCAUX
5V->1V35 LDO Used by: FPGA VCCIO2 + VCCIO3 SDRAM: 220mA
700mA max
300mA max
TODO: verify power up order: 5V->1V1 1V1->3V3/2V5/1V35 1V35->VTT
TODO: add RC filter to each rail to get a real PGOOD Some ICs have different high-level thresholds!
FPGA_VCC
FPGA_VCCIO0
FPGA_VCCIO6
TN1068 is shit, "use a bunch and vary per pin" :/ This mix taken from TinyFPGA.
Placed on backside, can be 0201
FPGA_VCCIO1
FPGA_VCCIO7
FPGA Decoupling Caps
FPGA Core Power
FPGA_VCCIO2
FPGA_VCCIO8 / Config
FPGA_VCCAUX
FPGA_VCCIO3
